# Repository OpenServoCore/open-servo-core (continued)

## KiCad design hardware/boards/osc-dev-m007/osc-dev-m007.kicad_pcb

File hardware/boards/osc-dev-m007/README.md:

# OSC Dev M007 - Rev A

> ⚠️ **Designed, not fabricated yet.**
> No physical copy of this board has been built or tested. Everything below is design intent, written before the first article. If you fab one before that happens, you are the test pilot.

The development board for OpenServoCore's M007 servo brain. One chip - the CH32M007, 3 × 3 mm - contains the microcontroller, the motor gate driver, the current-sense amplifier, and the 5 V regulator. Add six small MOSFETs and it drives a brushed servo motor (SG90/MG90 class) or a small 3-phase BLDC, measures motor current, reads a position sensor, and talks on a single-wire bus.

This is the bench version: everything on a labelled connector or test point, screw terminals for the motor, room to probe. The matching production board ([osc-sg90-m007](../osc-sg90-m007/)) squeezes the same circuit into an SG90 case; this one spreads it out on 50 × 50 mm so it is easy to work on.

## What you need

- **Power between 6.5 and 15 V** - a 2S or 3S LiPo, or a bench supply.
- A **WCH-LinkE** debug probe (about $4) to flash firmware and read logs.
- Something to move: a gutted hobby servo (motor + potentiometer), a bare DC motor, or a small gimbal-class BLDC.

## Board tour

Every connector is labelled on the silkscreen:

| Silk label | What it is |
| --- | --- |
| `+` `-` (JST, top left) | Battery input, 6.5-15 V, reverse-polarity protected |
| `A B C` (screw terminal) | Motor. Brushed motor uses A and B; BLDC uses all three |
| `DATA VS GND` (two JSTs) | The servo bus. Two jacks so boards daisy-chain; `VS` is the raw supply rail |
| `POT 5V GND` | Servo potentiometer (wiper to `POT`) |
| `ENC 5V GND` | Encoder input - analog voltage, or PWM like an AS5600 |
| `INT NTC EXT` | Temperature source jumper: onboard sensor (`INT`) or your own thermistor on the `NTC GND` header (`EXT`) |
| `SWDIO G 5V G RST` | Debug/flash header for the WCH-LinkE |
| `G VRG G VS G 5V` | Power-rail probe header, every second pin is ground |
| `NTC POS ENC LED GND DATA` | Signal breakout for a scope or logic analyzer |
| `DB0` `DB1` `DB2` + `GND` | Firmware timing probe pads |
| `RGB` | WS2812 status LED |
| `VS` / `5V` LEDs | Power indicators: motor rail / logic rail |
| `RESET` | Reset button |

## Powering it

Three ways in, and they can be combined freely:

1. **Battery jack** - 2S or 3S LiPo. This input has a protection diode, so a reversed pack does nothing instead of damage. The diode costs ~0.4 V, so a nearly-empty 2S may dip under the motor's 6.5 V floor a little early.
2. **Bus jack `VS` pin** - wired straight to the rail, no diode. This is how a servo receives power in a robot, and the better path for high-current bench work.
3. **The LinkE's 5 V** through the debug header - powers the logic only.

The one rule to internalize: **the motor only runs above about 6.5 V.** The gate driver refuses to switch below that - a built-in safety property, not a fault. In practice:

- On 5 V from the LinkE, everything except the motor works: the MCU boots, firmware flashes, the bus talks, sensors read. **A dark motor on USB-level power is normal, not a broken board.**
- A 1S battery (4.2 V) can never drive the motor. 2S minimum.

The FETs are sized for roughly 2 A continuous and 3 A bursts - enough for every SG90/MG90/MG996R-class servo. A hardware comparator cuts the bridge at about 2.5-2.75 A on its own, even if firmware hangs.

## Hooking up a servo

The core experiment - turning a $2 servo into a smart one:

1. Open the servo and unsolder its factory PCB.
2. Motor wires → screw terminals `A` and `B`.
3. Potentiometer → the `POT 5V GND` header, wiper to `POT`.
4. Power and bus → one of the JST bus jacks.

The board measures motor current through two small shunt resistors and the chip's built-in amplifier - about 1 mA per ADC count - so firmware can feel load and stall without any extra parts.

For temperature, the onboard sensor (`INT` jumper) tracks the board. For motor experiments, tape a 10 k NTC thermistor to the motor can, wire it to `NTC GND`, and move the jumper to `EXT`.

## Talking to it

The bus is one shared 5 V wire plus power and ground. Every servo hangs on the same three wires, each with its own address, at up to 3 Mbaud. The wire format is the [osc-native protocol](../../../docs/osc-native-protocol.md) - OSC's own break-framed protocol, in the spirit of Dynamixel but designed for very cheap MCUs.

On the host side, a second WCH-LinkE flashed with the [adapter firmware](../../../firmware/boards/osc-adapter-wchlinke/) becomes the USB-to-bus interface.

## Flashing firmware

Connect a WCH-LinkE to the debug header - `SWDIO` and `G` at minimum, plus `5V` if the probe should power the board - and flash with [wlink](https://github.com/ch32-rs/wlink). Firmware v2 for the M007 is in bring-up; the transport and protocol layers are proven on the V006 family and the M007 uses the same USART hardware. Check the repo root [README](../../../README.md) for current status.

## Specs

| | |
| --- | --- |
| Brain | CH32M007E8U7 - 48 MHz RISC-V MCU + gate driver + current-sense amp + 5 V regulator, one QFN-26 |
| Supply | 6.5-15 V (2S/3S LiPo) |
| Motor | Brushed H-bridge or 3-phase BLDC, ~2 A continuous / 3 A burst |
| Current sense | Two 75 mΩ shunts, on-die amplifier, ~1 mA resolution |
| Overcurrent | Hardware comparator trip at ~2.5-2.75 A |
| Feedback | Potentiometer, analog/PWM encoder, NTC (onboard or external) |
| Bus | Single-wire half-duplex, 5 V logic, 0.5-3 Mbaud |
| Size | 50 × 50 mm, 6-layer, M2 mounting holes |

## Building one

The board is designed around JLCPCB's 6-layer promo: 50 × 50 mm, all vias 0.3 mm, epoxy-filled vias (select "Epoxy Filled & Capped"), which prices at a few dollars for five boards and forces ENIG (gold) finish - which also makes hand assembly nicer.

- Every part has its LCSC number in the schematic; the passives are 0805, chosen for easy hand soldering.
- One genuinely hard joint: the QFN-26 with its center pad. That pad ties into the board's internal copper planes, which soak up heat - hot air from the top alone usually can't get the joint to reflow. Heat the board from below with a hotplate (paste stencil, place the chip, reflow the whole side), using hot air on top only as a finisher. Everything else is beginner-friendly.
- Parts marked DNP ("do not populate") in the schematic are options and tuning pads. Leave them empty - that IS the standard build. Some of them change how the board behaves (shunt value, sense filtering), so only mount one if you know exactly why you want it.

## More reading

- [osc-native protocol](../../../docs/osc-native-protocol.md) - the wire protocol
- [servo transport](../../../docs/osc-servo-transport.md) - how the servo side keeps up at 3 Mbaud
- [design history](../../../docs/design-history.md) - how the project got here

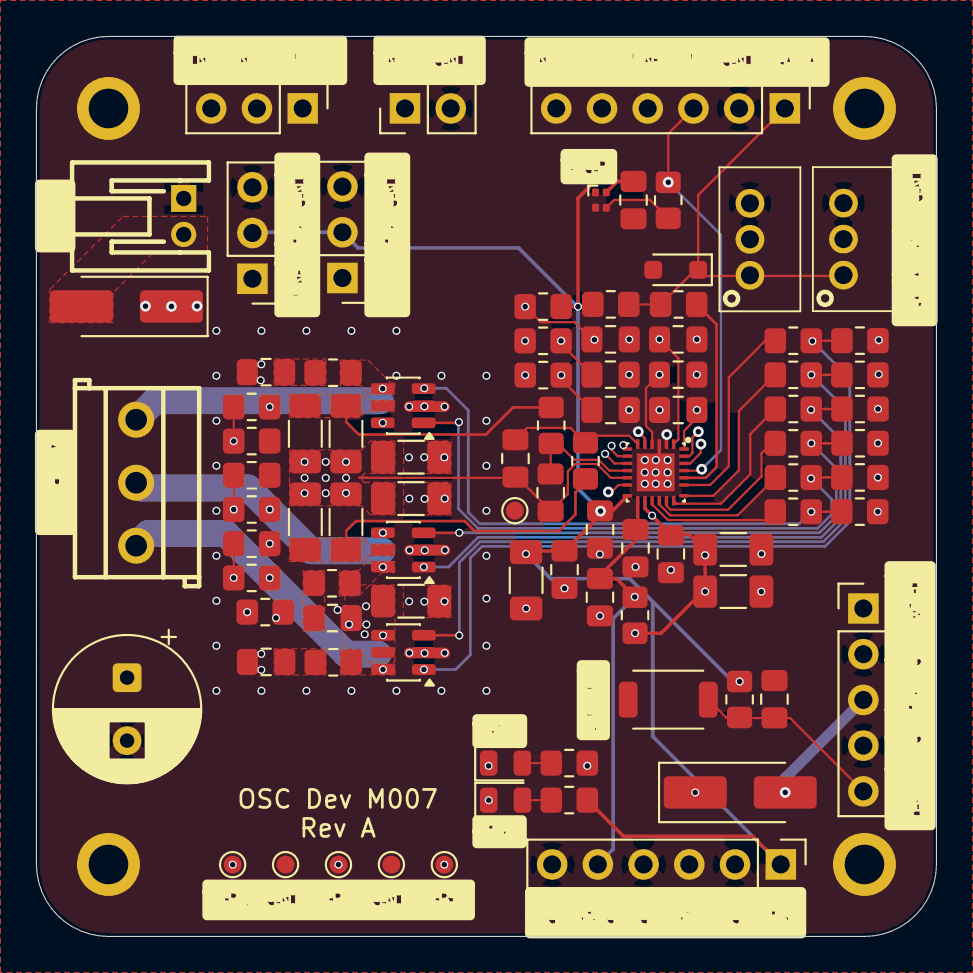
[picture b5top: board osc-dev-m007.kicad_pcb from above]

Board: 6 copper layers, 50.0 x 50.0 mm, 99 parts (0 on the bottom side), 52 nets.

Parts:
C201, C202: 2.2uF; C_0805_2012Metric_Pad1.18x1.45mm_HandSolder
C203, C206, C209, C210, C1002, C1003: 0.1uF; C_0805_2012Metric_Pad1.18x1.45mm_HandSolder
C204, C205, C208, C401, C601, C801: 10uF; C_1206_3216Metric_Pad1.33x1.80mm_HandSolder
C207: 1uF; C_0805_2012Metric_Pad1.18x1.45mm_HandSolder
C301: 470uF 25V; CP_Radial_D8.0mm_P3.50mm
C402, C403, C501, C602, C603, C701, C802, C803, C1001: 1nF; C_0805_2012Metric_Pad1.18x1.45mm_HandSolder
D201: STAT; LED_XL-1010RGBC-WS2812B_1x1mm
D901, D902: SS54; D_SMA_Handsoldering
D1101: PESD5V0L1BA; D_SOD-323_HandSoldering
H101, H102, H103, H104: MountingHole_Pad_MP; MountingHole_2.2mm_M2_ISO7380_Pad
J201: PROG; PinHeader_1x05_P2.54mm_Vertical
J301: BLDC/BDC(A+B); CONN-TH_3P-P3.50_KF350-3.5-3P
J901: JST-PH-H; CONN-TH_S2B-PH-K-S-LF-SN
J1001: NTC_EXT; PinHeader_1x02_P2.54mm_Vertical
J1002: ENC; PinHeader_1x03_P2.54mm_Vertical
J1003: POT; PinHeader_1x03_P2.54mm_Vertical
J1101, J1102: JST-PH-V; CONN-TH_B3B-PH-K-S
J1201, J1202: Conn_01x06; PinHeader_1x06_P2.54mm_Vertical
JP1001: NTC_EXT_INT; PinHeader_1x03_P2.54mm_Vertical
LED901: YELLOW; LED_0805_2012Metric
LED902: GREEN; LED_0805_2012Metric
NT501, NT502, NT701, NT702: NetTie_2; NetTie-2_SMD_0.127mm
Q401, Q601, Q801: SIL3724A-TP; SOT-23-6
R201, R401, R402, R501, R601, R602, R701, R801, R802: 0; R_0805_2012Metric_Pad1.20x1.40mm_HandSolder
R202, R406, R606, R806, R902, R1001, R1102: 10k; R_0805_2012Metric_Pad1.20x1.40mm_HandSolder
R203: 100; R_0805_2012Metric_Pad1.20x1.40mm_HandSolder
R403, R404, R603, R604, R803, R804: 100k; R_0805_2012Metric_Pad1.20x1.40mm_HandSolder
R405, R605, R805: 20k; R_0805_2012Metric_Pad1.20x1.40mm_HandSolder
R407, R607, R807: 10; R_0805_2012Metric_Pad1.20x1.40mm_HandSolder
R901: 22k; R_0805_2012Metric_Pad1.20x1.40mm_HandSolder
R1002, R1003: 4.7k; R_0805_2012Metric_Pad1.20x1.40mm_HandSolder
R1101: 33; R_0805_2012Metric_Pad1.20x1.40mm_HandSolder
R_SH501, R_SH701: 75m; R_1206_3216Metric_Pad1.30x1.75mm_HandSolder
R_SH502, R_SH702: 150m; R_1206_3216Metric_Pad1.30x1.75mm_HandSolder
SW201: RESET; SW_SPST_TS-1088R_3.9x3.0mm
TH1001: 10k 3950K; R_0805_2012Metric_Pad1.20x1.40mm_HandSolder
TP1201, TP1202, TP1203, TP1204, TP1205, TP1206: TestPoint; TestPoint_Pad_D1.0mm
U201: CH32M007E8U7; QFN-26_3x3mm_P0.4mm

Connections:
+5V: C206.1, C207.1, C208.1, C210.1, D201.2 (VDD), J1002.2, J1003.2, J1201.1, R202.1, R902.1, R1001.1, R1102.1, U201.13 (VDD)
/BRIDGE/HALFBRIDGE1/G_H: Q401.3 (G), R401.2, R403.1
/BRIDGE/HALFBRIDGE1/G_L: Q401.1 (G), R402.2, R404.2
/BRIDGE/HALFBRIDGE1/LEG: NT501.1, Q401.5 (S), R_SH501.1, R_SH502.1
/BRIDGE/HALFBRIDGE1/SNUB: C403.1, R407.2
/BRIDGE/HALFBRIDGE2/G_H: Q601.3 (G), R601.2, R603.1
/BRIDGE/HALFBRIDGE2/G_L: Q601.1 (G), R602.2, R604.2
/BRIDGE/HALFBRIDGE2/LEG: NT701.1, Q601.5 (S), R_SH701.1, R_SH702.1
/BRIDGE/HALFBRIDGE2/SNUB: C603.1, R607.2
/BRIDGE/HALFBRIDGE3/G_H: Q801.3 (G), R801.2, R803.1
/BRIDGE/HALFBRIDGE3/G_L: Q801.1 (G), R802.2, R804.2
/BRIDGE/HALFBRIDGE3/SNUB: C803.1, R807.2
/BRIDGE/PH_A: J301.1, Q401.4 (D), Q401.6 (D), R405.1, R407.1
/BRIDGE/PH_B: J301.2, Q601.4 (D), Q601.6 (D), R605.1, R607.1
/BRIDGE/PH_C: J301.3, Q801.4 (D), Q801.6 (D), R805.1, R807.1
/BRIDGE/SHUNT1/ISNS_K: NT501.2, R501.1
/BRIDGE/SHUNT2/ISNS_K: NT701.2, R701.1
/BUS/BUS: R1101.2, U201.22 (TX_5)
/MCU/SWDIO: J201.1, U201.5 (SWIO)
/MCU/nRST: C209.2, J201.5, R202.2, SW201.2, U201.2 (RST)
/POWER/LED_5V: LED902.2 (A), R902.2
/POWER/LED_VSYS: LED901.2 (A), R901.2
/SENSORS/ENC_IN: J1002.1, R1002.2
/SENSORS/NTC_EXT: J1001.1, JP1001.1 (A)
/SENSORS/NTC_INT: JP1001.3 (B), TH1001.1
/SENSORS/POT: J1003.1, R1003.2
DATA: D1101.1 (K), J1101.1, J1102.1, J1202.1, R1101.1, R1102.2
DBG0: TP1201.1 (1_1), U201.25 (PC2)
DBG1: TP1203.1 (1_1), U201.12 (PA5)
DBG2: TP1205.1 (1_1), U201.24 (PC1)
ENC: C1001.2, J1202.4, R1002.1, U201.7 (A7)
GATE_AH: R401.1, U201.16 (HO1)
GATE_AL: R402.1, U201.17 (LO1)
GATE_BH: R601.1, U201.18 (HO2)
GATE_BL: R602.1, U201.19 (LO2)
GATE_CH: R801.1, U201.20 (HO3)
GATE_CL: R802.1, U201.21 (LO3)
GND: C201.2, C202.2, C203.2, C204.2, C205.2, C206.2, C207.2, C208.2, C209.1, C210.2, C301.2, C401.2, C402.2, C403.2, C601.2, C602.2, C603.2, C801.2, C802.2, C803.2, C1001.1, C1002.1, C1003.1, D201.3 (VSS), D1101.2 (A), H101.1 (1_1), H102.1 (1_1), H103.1 (1_1), H104.1 (1_1), J201.2, J201.4, J901.1, J1001.2, J1002.3, J1003.3, J1101.3, J1102.3, J1201.2, J1201.4, J1201.6, J1202.2, LED901.1 (K), LED902.1 (K), NT502.1, NT702.1, Q801.5 (S), R404.1, R406.2, R604.1, R606.2, R804.1, R806.2, R_SH501.2, R_SH502.2, R_SH701.2, R_SH702.2, SW201.1, TH1001.2, TP1202.1 (1_1), TP1204.1 (1_1), TP1206.1 (1_1), U201.3 (VSS)
ISNS1+: C501.1, R501.2, U201.10 (OPP1)
ISNS2+: C701.1, R701.2, U201.6 (OPP2)
ISNS-: C501.2, C701.2, NT502.2, NT702.2, U201.11 (OPN2)
LED: J1202.3, R203.1, U201.23 (T2C3_01)
NTC: C1003.2, J1202.6, JP1001.2 (C), R1001.2, U201.9 (A6)
unnamed: D201.4 (DIN), R203.2
POS: C1002.2, J1202.5, R1003.1, U201.8 (A5)
VBAT: D901.2 (A), J901.2
VHREG: C201.1, C202.1, J1201.5, R201.1, U201.14 (VHREG)
VPROG: D902.2 (A), J201.3
VSNA: C402.1, R405.2, R406.1, U201.1 (A2)
VSNB: C602.1, R605.2, R606.1, U201.4 (A3)
VSNC: C802.1, R805.2, R806.1, U201.26 (A1)
VSYS: C203.1, C204.1, C205.1, C301.1, C401.1, C601.1, C801.1, D901.1 (K), D902.1 (K), J1101.2, J1102.2, J1201.3, Q401.2 (S), Q601.2 (S), Q801.2 (S), R201.2, R403.2, R603.2, R803.2, R901.1, U201.15 (VHV)

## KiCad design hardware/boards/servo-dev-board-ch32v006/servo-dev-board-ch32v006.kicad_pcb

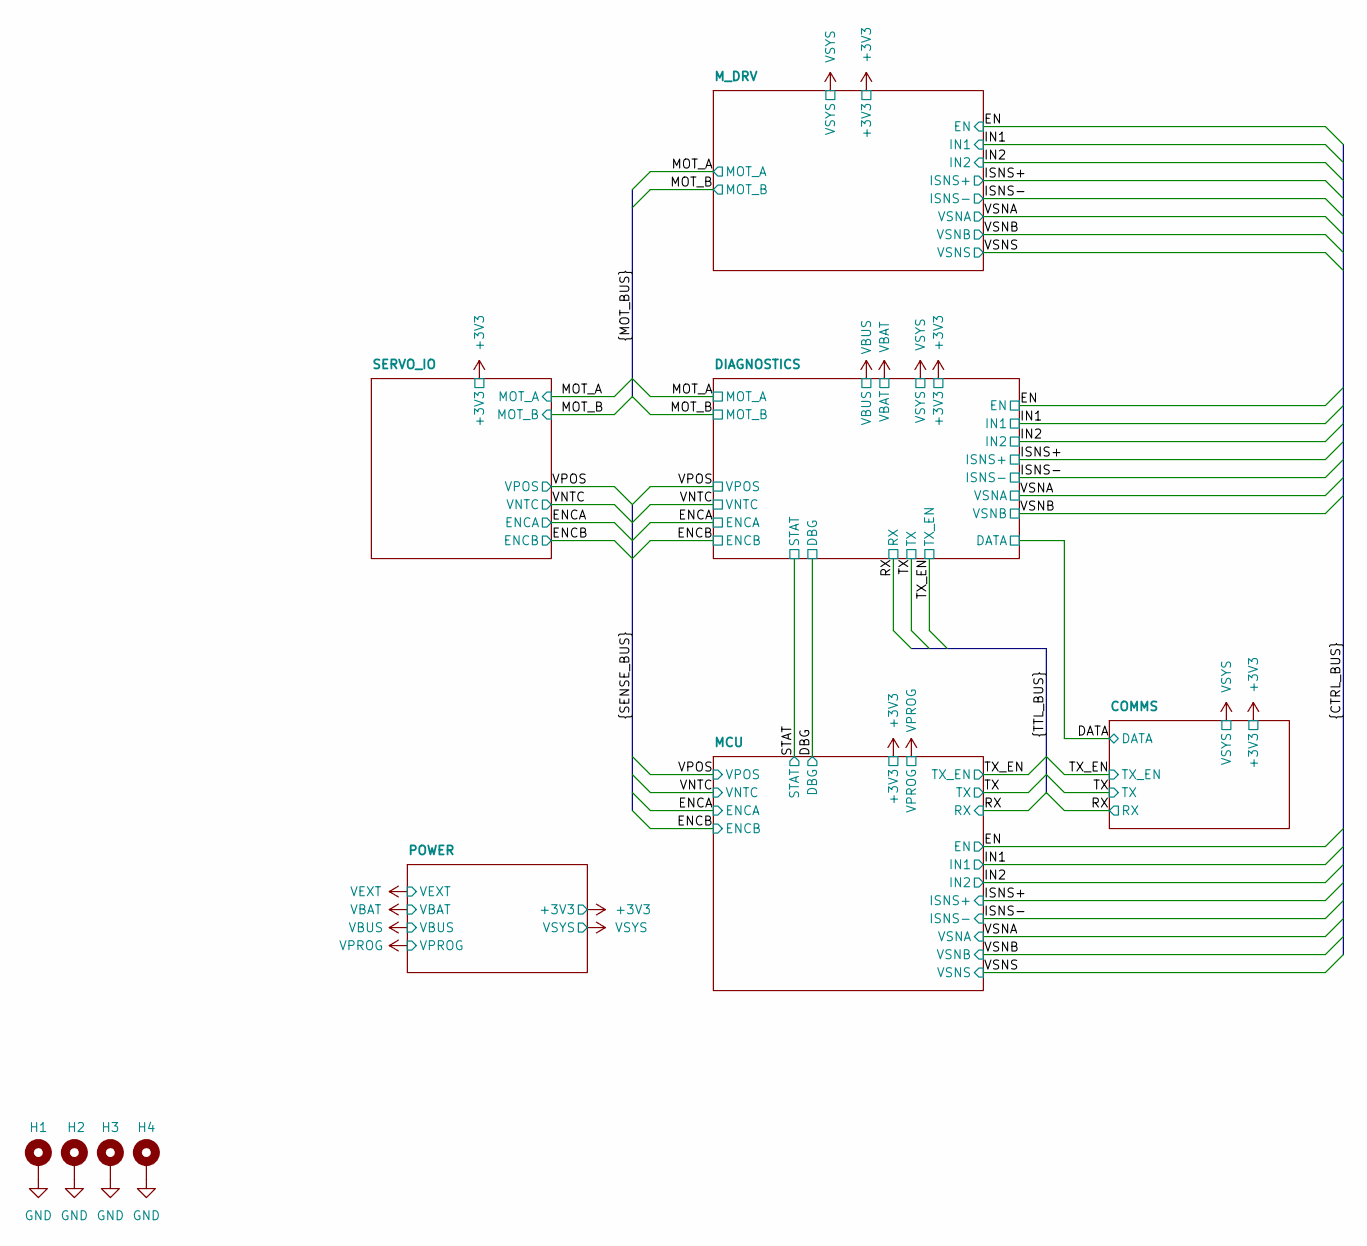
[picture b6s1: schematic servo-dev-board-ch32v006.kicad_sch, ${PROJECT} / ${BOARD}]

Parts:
H1, H2, H3, H4: MountingHole_Pad_MP; MountingHole_2.2mm_M2_ISO7380_Pad

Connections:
GND: H1.1 (1_1), H2.1 (1_1), H3.1 (1_1), H4.1 (1_1); also elsewhere on the board

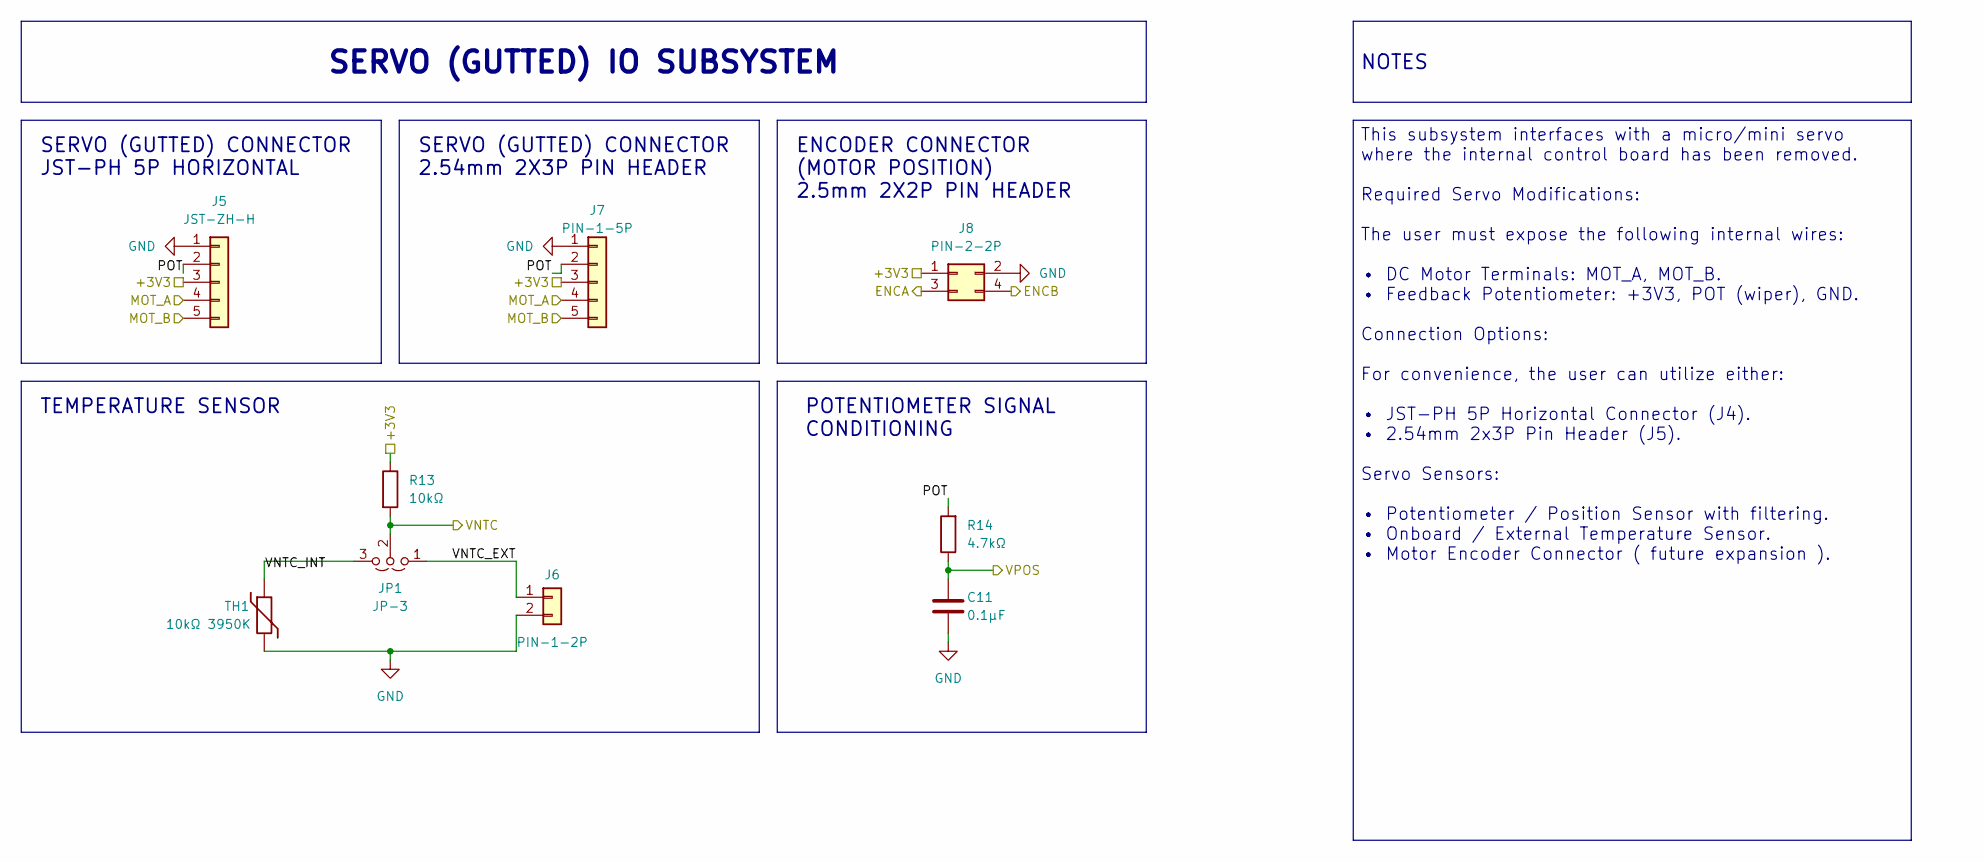
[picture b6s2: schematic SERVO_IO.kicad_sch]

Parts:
C11: 0.1µF; C_0805_2012Metric_Pad1.18x1.45mm_HandSolder; LCSC C28233
J5: JST-ZH-H; CONN-TH_S5B-ZR-LF-SN; JLC Type Extended
J6: PIN-1-2P; PinHeader_1x02_P2.54mm_Vertical; LCSC C492401
J7: PIN-1-5P; PinHeader_1x05_P2.54mm_Vertical; LCSC C42431812
J8: PIN-2-2P; PinHeader_2x02_P2.54mm_Vertical; LCSC C66690
JP1: JP-3; PinHeader_1x03_P2.54mm_Vertical; LCSC C41425293
R13: 10kΩ; R_0805_2012Metric_Pad1.20x1.40mm_HandSolder; LCSC C17414
R14: 4.7kΩ; R_0805_2012Metric_Pad1.20x1.40mm_HandSolder; LCSC C17673
TH1: 10kΩ 3950K; R_0805_2012Metric_Pad1.20x1.40mm_HandSolder; LCSC C95968

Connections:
+3V3: J5.3, J7.3, J8.1, R13.1; also elsewhere on the board
/ENCA: J8.3; also elsewhere on the board
/ENCB: J8.4; also elsewhere on the board
/MOT_A: J5.4, J7.4; also elsewhere on the board
/MOT_B: J5.5, J7.5; also elsewhere on the board
/SERVO_IO/POT: J5.2, J7.2, R14.2
/SERVO_IO/VNTC_EXT: J6.1, JP1.1 (A)
/SERVO_IO/VNTC_INT: JP1.3 (B), TH1.1
/VNTC: JP1.2 (C), R13.2; also elsewhere on the board
/VPOS: C11.1, R14.1; also elsewhere on the board
GND: C11.2, J5.1, J6.2, J7.1, J8.2, TH1.2; also elsewhere on the board

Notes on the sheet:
SERVO (GUTTED) CONNECTOR 2.54mm 2X3P PIN HEADER
ENCODER CONNECTOR (MOTOR POSITION) 2.5mm 2X2P PIN HEADER
TEMPERATURE SENSOR
POTENTIOMETER SIGNAL CONDITIONING
SERVO (GUTTED) CONNECTOR JST-PH 5P HORIZONTAL
This subsystem interfaces with a micro/mini servo where the internal control board has been removed. Required Servo Modifications: The user must expose the following internal wires: • DC Motor Terminals: MOT_A, MOT_B. • Feedback Potentiometer: +3V3, POT (wiper), GND. Connection Options: For conveni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
NOTES
SERVO (GUTTED) IO SUBSYSTEM

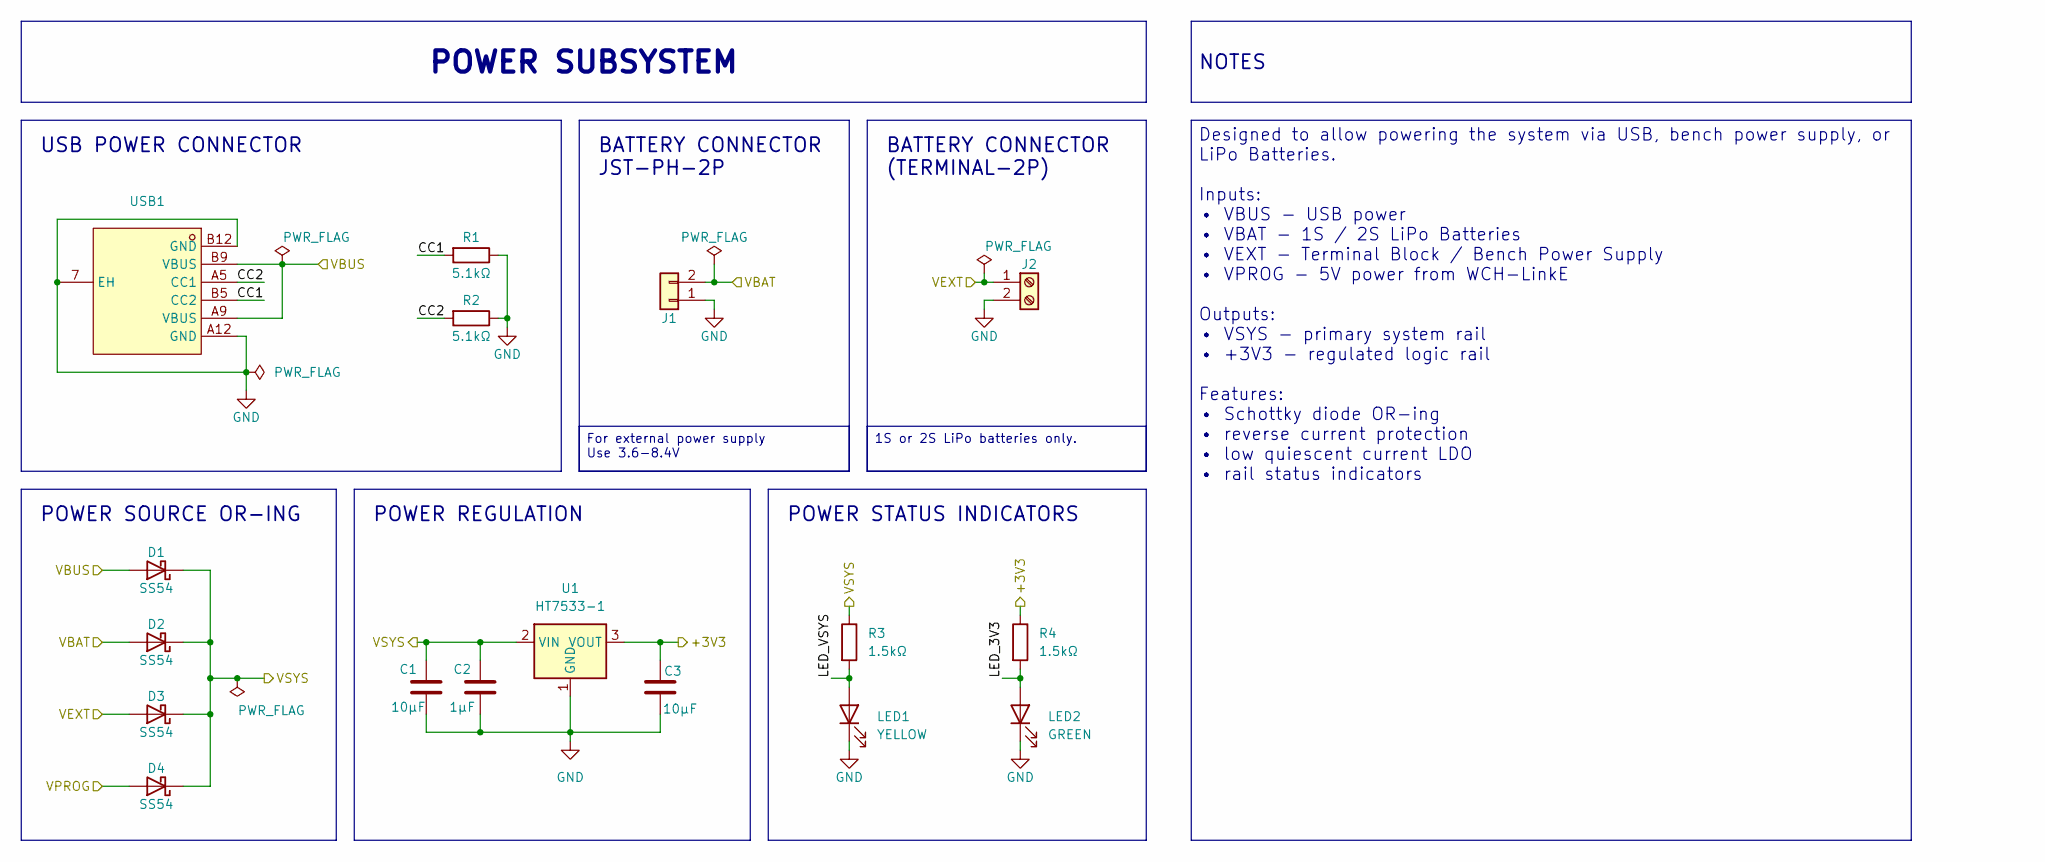
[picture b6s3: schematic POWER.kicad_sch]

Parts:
C1, C3: 10µF; C_0805_2012Metric_Pad1.18x1.45mm_HandSolder; LCSC C440198
C2: 1µF; C_0805_2012Metric_Pad1.18x1.45mm_HandSolder; LCSC C28323
D1, D2, D3, D4: SS54; D_SMA_Handsoldering; LCSC C22452
J1: JST-PH-H; CONN-TH_S2B-PH-K-S-LF-SN; LCSC C173752
J2: TERM; CONN-TH_2P-P5.00_WJ500V-5.08-2P; LCSC C8465
LED1: YELLOW; LED_0805_2012Metric; LCSC C2296
LED2: GREEN; LED_0805_2012Metric; LCSC C2297
R1, R2: 5.1kΩ; R_0805_2012Metric_Pad1.20x1.40mm_HandSolder; LCSC C27834
R3, R4: 1.5kΩ; R_0805_2012Metric_Pad1.20x1.40mm_HandSolder; LCSC C4310
U1: HT7533-1; SOT-89-3_Handsoldering; LCSC C14289
USB1: TYPE-C-H; TYPE-C-SMD_TYPE-C-6P-073; LCSC C668623

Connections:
+3V3: C3.1, R4.1, U1.3 (VOUT); also elsewhere on the board
/POWER/CC1: R1.2, USB1.B5 (CC2)
/POWER/CC2: R2.2, USB1.A5 (CC1)
/POWER/LED_3V3: LED2.2 (A), R4.2
/POWER/LED_VSYS: LED1.2 (A), R3.2
GND: C1.2, C2.2, C3.2, J1.1, J2.2, LED1.1 (K), LED2.1 (K), R1.1, R2.1, U1.1 (GND), USB1.7 (EH), USB1.A12 (GND), USB1.B12 (GND); also elsewhere on the board
VBAT: D2.2 (A), J1.2; also elsewhere on the board
VBUS: D1.2 (A), USB1.A9 (VBUS), USB1.B9 (VBUS); also elsewhere on the board
VEXT: D3.2 (A), J2.1
VPROG: D4.2 (A); also elsewhere on the board
VSYS: C1.1, C2.1, D1.1 (K), D2.1 (K), D3.1 (K), D4.1 (K), R3.1, U1.2 (VIN); also elsewhere on the board

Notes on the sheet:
BATTERY CONNECTOR JST-PH-2P
BATTERY CONNECTOR (TERMINAL-2P)
POWER REGULATION
POWER STATUS INDICATORS
USB POWER CONNECTOR
POWER SOURCE OR-ING
NOTES
Designed to allow powering the system via USB, bench power supply, or LiPo Batteries. Inputs: • VBUS - USB power • VBAT - 1S / 2S LiPo Batteries • VEXT - Terminal Block / Bench Power Supply • VPROG - 5V power from WCH-LinkE Outputs: • VSYS - primary system rail • +3V3 - regulated logic rail Feature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
POWER SUBSYSTEM
For external power supply Use 3.6-8.4V
1S or 2S LiPo batteries only.

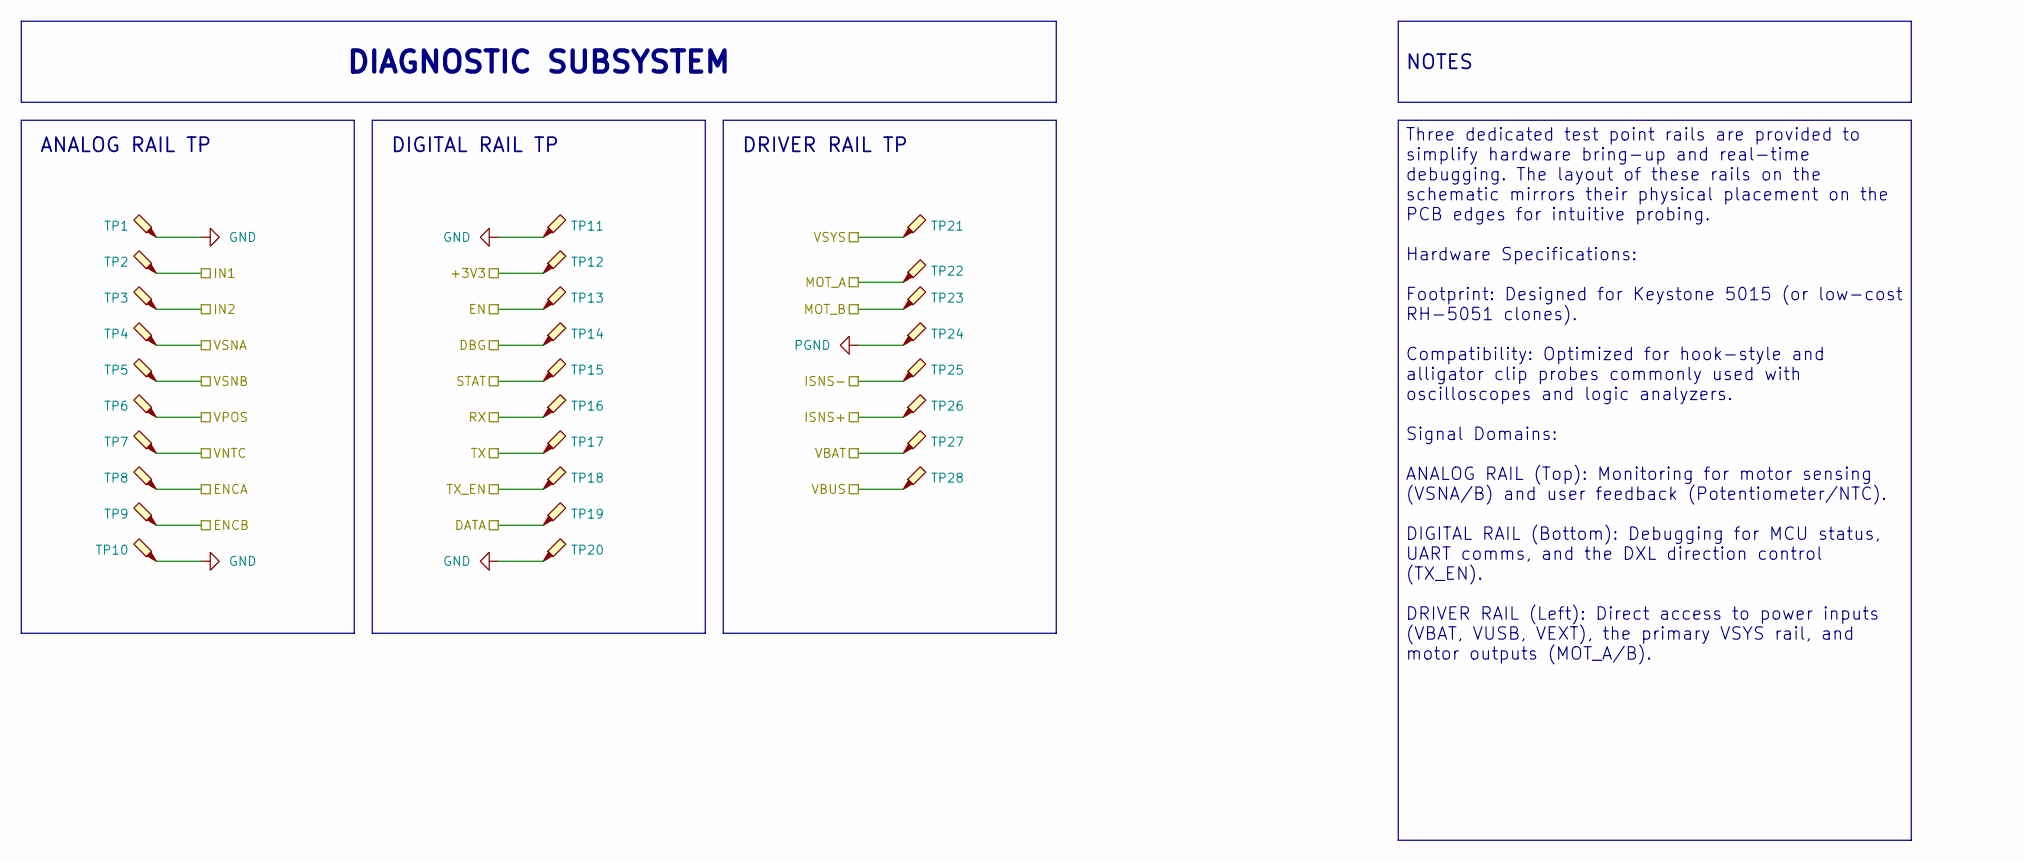
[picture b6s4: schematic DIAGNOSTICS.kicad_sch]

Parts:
TP1, TP2, TP3, TP4, TP5, TP6, TP7, TP8, TP9, TP10, TP11, TP12, TP13, TP14, TP15, TP16, TP17, TP18, TP19, TP20, TP21, TP22, TP23, TP24, TP25, TP26, TP27, TP28: TestPoint_Probe; TestPoint_Keystone_5015_Micro_Mini; LCSC C5199798

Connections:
+3V3: TP12.1 (1_1); also elsewhere on the board
/DATA: TP19.1 (1_1); also elsewhere on the board
/DBG: TP14.1 (1_1); also elsewhere on the board
/EN: TP13.1 (1_1); also elsewhere on the board
/ENCA: TP8.1 (1_1); also elsewhere on the board
/ENCB: TP9.1 (1_1); also elsewhere on the board
/IN1: TP2.1 (1_1); also elsewhere on the board
/IN2: TP3.1 (1_1); also elsewhere on the board
/ISNS+: TP26.1 (1_1); also elsewhere on the board
/ISNS-: TP25.1 (1_1); also elsewhere on the board
/MOT_A: TP22.1 (1_1); also elsewhere on the board
/MOT_B: TP23.1 (1_1); also elsewhere on the board
/RX: TP16.1 (1_1); also elsewhere on the board
/STAT: TP15.1 (1_1); also elsewhere on the board
/TX: TP17.1 (1_1); also elsewhere on the board
/TX_EN: TP18.1 (1_1); also elsewhere on the board
/VNTC: TP7.1 (1_1); also elsewhere on the board
/VPOS: TP6.1 (1_1); also elsewhere on the board
/VSNA: TP4.1 (1_1); also elsewhere on the board
/VSNB: TP5.1 (1_1); also elsewhere on the board
GND: TP1.1 (1_1), TP10.1 (1_1), TP11.1 (1_1), TP20.1 (1_1); also elsewhere on the board
PGND: TP24.1 (1_1); also elsewhere on the board
VBAT: TP27.1 (1_1); also elsewhere on the board
VBUS: TP28.1 (1_1); also elsewhere on the board
VSYS: TP21.1 (1_1); also elsewhere on the board

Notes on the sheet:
ANALOG RAIL TP
DRIVER RAIL TP
DIGITAL RAIL TP
DIAGNOSTIC SUBSYSTEM
NOTES
Three dedicated test point rails are provided to simplify hardware bring-up and real-time debugging. The layout of these rails on the schematic mirrors their physical placement on the PCB edges for intuitive probing. Hardware Specifications: Footprint: Designed for Keystone 5015 (or low-cost RH-505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

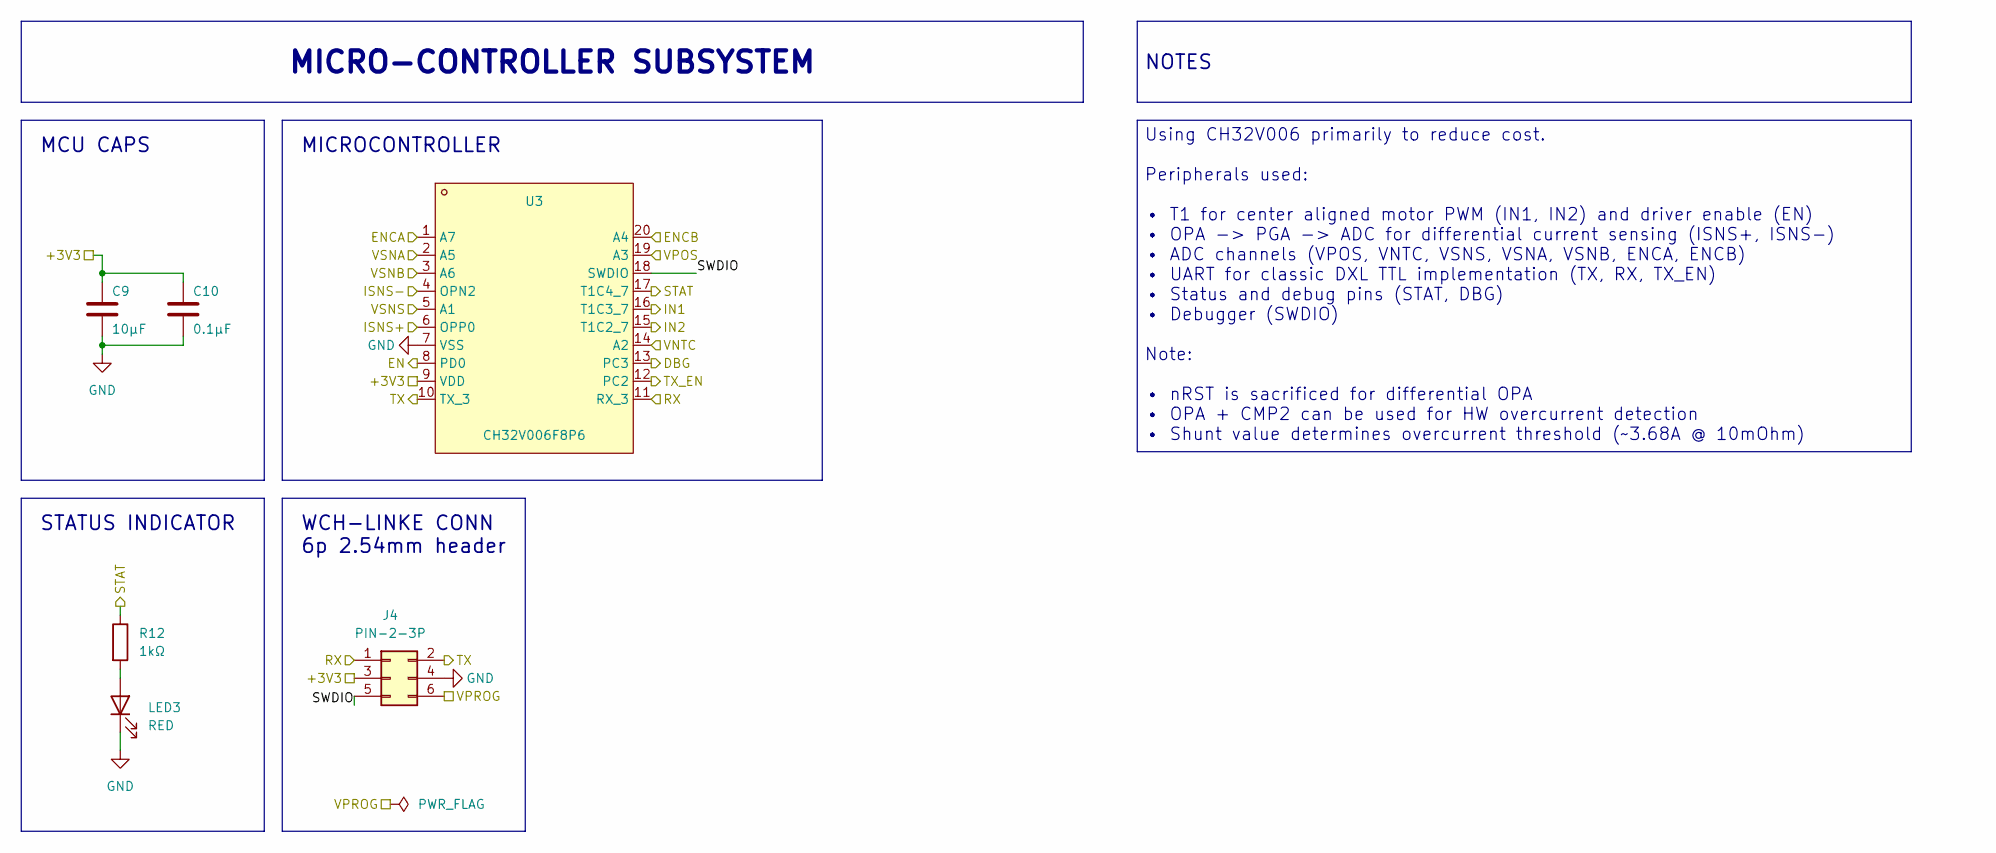
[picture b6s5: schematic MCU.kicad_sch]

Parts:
C9: 10µF; C_0805_2012Metric_Pad1.18x1.45mm_HandSolder; LCSC C440198
C10: 0.1µF; C_0805_2012Metric_Pad1.18x1.45mm_HandSolder; LCSC C28233
J4: PIN-2-3P; PinHeader_2x03_P2.54mm_Vertical; LCSC C65114
LED3: RED; LED_0805_2012Metric; LCSC C84256
R12: 1kΩ; R_0805_2012Metric_Pad1.20x1.40mm_HandSolder; LCSC C17513
U3: CH32V006F8P6; TSSOP-20_4.4x6.5mm_P0.65mm; LCSC C52753342

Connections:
+3V3: C9.1, C10.1, J4.3, U3.9 (VDD); also elsewhere on the board
/DBG: U3.13 (PC3); also elsewhere on the board
/EN: U3.8 (PD0); also elsewhere on the board
/ENCA: U3.1 (A7); also elsewhere on the board
/ENCB: U3.20 (A4); also elsewhere on the board
/IN1: U3.16 (T1C3_7); also elsewhere on the board
/IN2: U3.15 (T1C2_7); also elsewhere on the board
/ISNS+: U3.6 (OPP0); also elsewhere on the board
/ISNS-: U3.4 (OPN2); also elsewhere on the board
/MCU/SWDIO: J4.5, U3.18 (SWDIO)
/RX: J4.1, U3.11 (RX_3); also elsewhere on the board
/STAT: R12.1, U3.17 (T1C4_7); also elsewhere on the board
/TX: J4.2, U3.10 (TX_3); also elsewhere on the board
/TX_EN: U3.12 (PC2); also elsewhere on the board
/VNTC: U3.14 (A2); also elsewhere on the board
/VPOS: U3.19 (A3); also elsewhere on the board
/VSNA: U3.2 (A5); also elsewhere on the board
/VSNB: U3.3 (A6); also elsewhere on the board
/VSNS: U3.5 (A1); also elsewhere on the board
GND: C9.2, C10.2, J4.4, LED3.1 (K), U3.7 (VSS); also elsewhere on the board
unnamed: LED3.2 (A), R12.2
VPROG: J4.6; also elsewhere on the board

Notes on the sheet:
MCU CAPS
MICROCONTROLLER
STATUS INDICATOR
WCH-LINKE CONN 6p 2.54mm header
NOTES
Using CH32V006 primarily to reduce cost. Peripherals used: • T1 for center aligned motor PWM (IN1, IN2) and driver enable (EN) • OPA -> PGA -> ADC for differential current sensing (ISNS+, ISNS-) • ADC channels (VPOS, VNTC, VSNS, VSNA, VSNB, ENCA, ENCB) • UART for classic DXL TTL implementation (TX,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
MICRO-CONTROLLER SUBSYSTEM

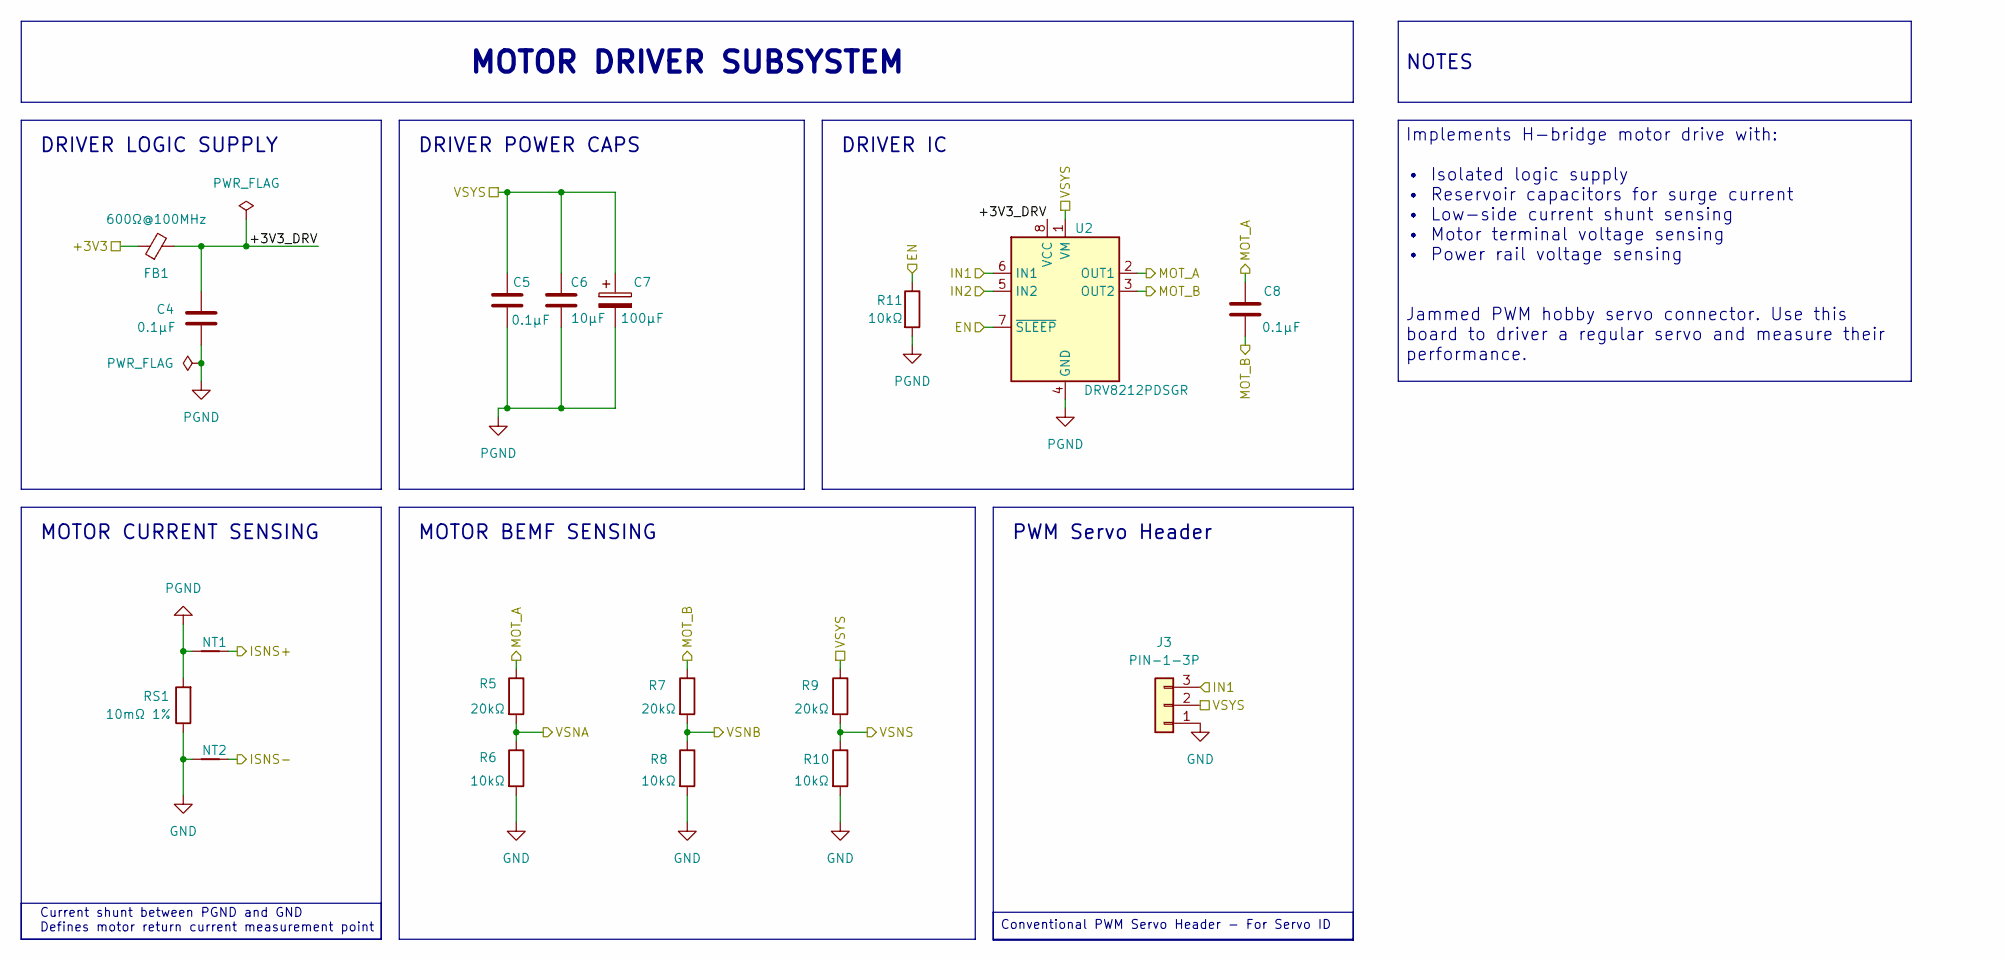
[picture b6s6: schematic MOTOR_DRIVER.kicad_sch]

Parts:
C4, C5, C8: 0.1µF; C_0805_2012Metric_Pad1.18x1.45mm_HandSolder; LCSC C28233
C6: 10µF; C_0805_2012Metric_Pad1.18x1.45mm_HandSolder; LCSC C440198
C7: 100µF; CP_Elec_6.3x5.4; LCSC C19271225
FB1: 600Ω@100MHz; L_0805_2012Metric_Pad1.05x1.20mm_HandSolder; LCSC C1017
J3: PIN-1-3P; PinHeader_1x03_P2.54mm_Vertical; LCSC C49257
NT1, NT2: NetTie_2; NetTie-2_SMD_0.2mm
R5, R7, R9: 20kΩ; R_0805_2012Metric_Pad1.20x1.40mm_HandSolder; LCSC C4328
R6, R8, R10, R11: 10kΩ; R_0805_2012Metric_Pad1.20x1.40mm_HandSolder; LCSC C17414
RS1: 10mΩ 1%; R_1206_3216Metric; LCSC C473031
U2: DRV8212PDSGR; WSON-8-1EP_2x2mm_P0.5mm_EP0.9x1.6mm; LCSC C5208051

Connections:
+3V3: FB1.1; also elsewhere on the board
/EN: R11.1, U2.7 (~SLEEP); also elsewhere on the board
/IN1: J3.3, U2.6 (IN1); also elsewhere on the board
/IN2: U2.5 (IN2); also elsewhere on the board
/ISNS+: NT1.1; also elsewhere on the board
/ISNS-: NT2.1; also elsewhere on the board
/MOT_A: C8.1, R5.1, U2.2 (OUT1); also elsewhere on the board
/MOT_B: C8.2, R7.1, U2.3 (OUT2); also elsewhere on the board
/M_DRV/+3V3_DRV: C4.1, FB1.2, U2.8 (VCC)
/VSNA: R5.2, R6.1; also elsewhere on the board
/VSNB: R7.2, R8.1; also elsewhere on the board
/VSNS: R9.2, R10.1; also elsewhere on the board
GND: J3.1, NT2.2, R6.2, R8.2, R10.2, RS1.1; also elsewhere on the board
PGND: C4.2, C5.2, C6.2, C7.2, NT1.2, R11.2, RS1.2, U2.4 (GND), U2.9 (GND); also elsewhere on the board
VSYS: C5.1, C6.1, C7.1, J3.2, R9.1, U2.1 (VM); also elsewhere on the board

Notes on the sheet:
MOTOR BEMF SENSING
Current shunt between PGND and GND Defines motor return current measurement point
DRIVER POWER CAPS
PWM Servo Header
DRIVER LOGIC SUPPLY
MOTOR CURRENT SENSING
DRIVER IC
Conventional PWM Servo Header - For Servo ID
MOTOR DRIVER SUBSYSTEM
NOTES
Implements H-bridge motor drive with: • Isolated logic supply • Reservoir capacitors for surge current • Low-side current shunt sensing • Motor terminal voltage sensing • Power rail voltage sensing Jammed PWM hobby servo connector. Use this board to driver a regular servo and measure their performa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
